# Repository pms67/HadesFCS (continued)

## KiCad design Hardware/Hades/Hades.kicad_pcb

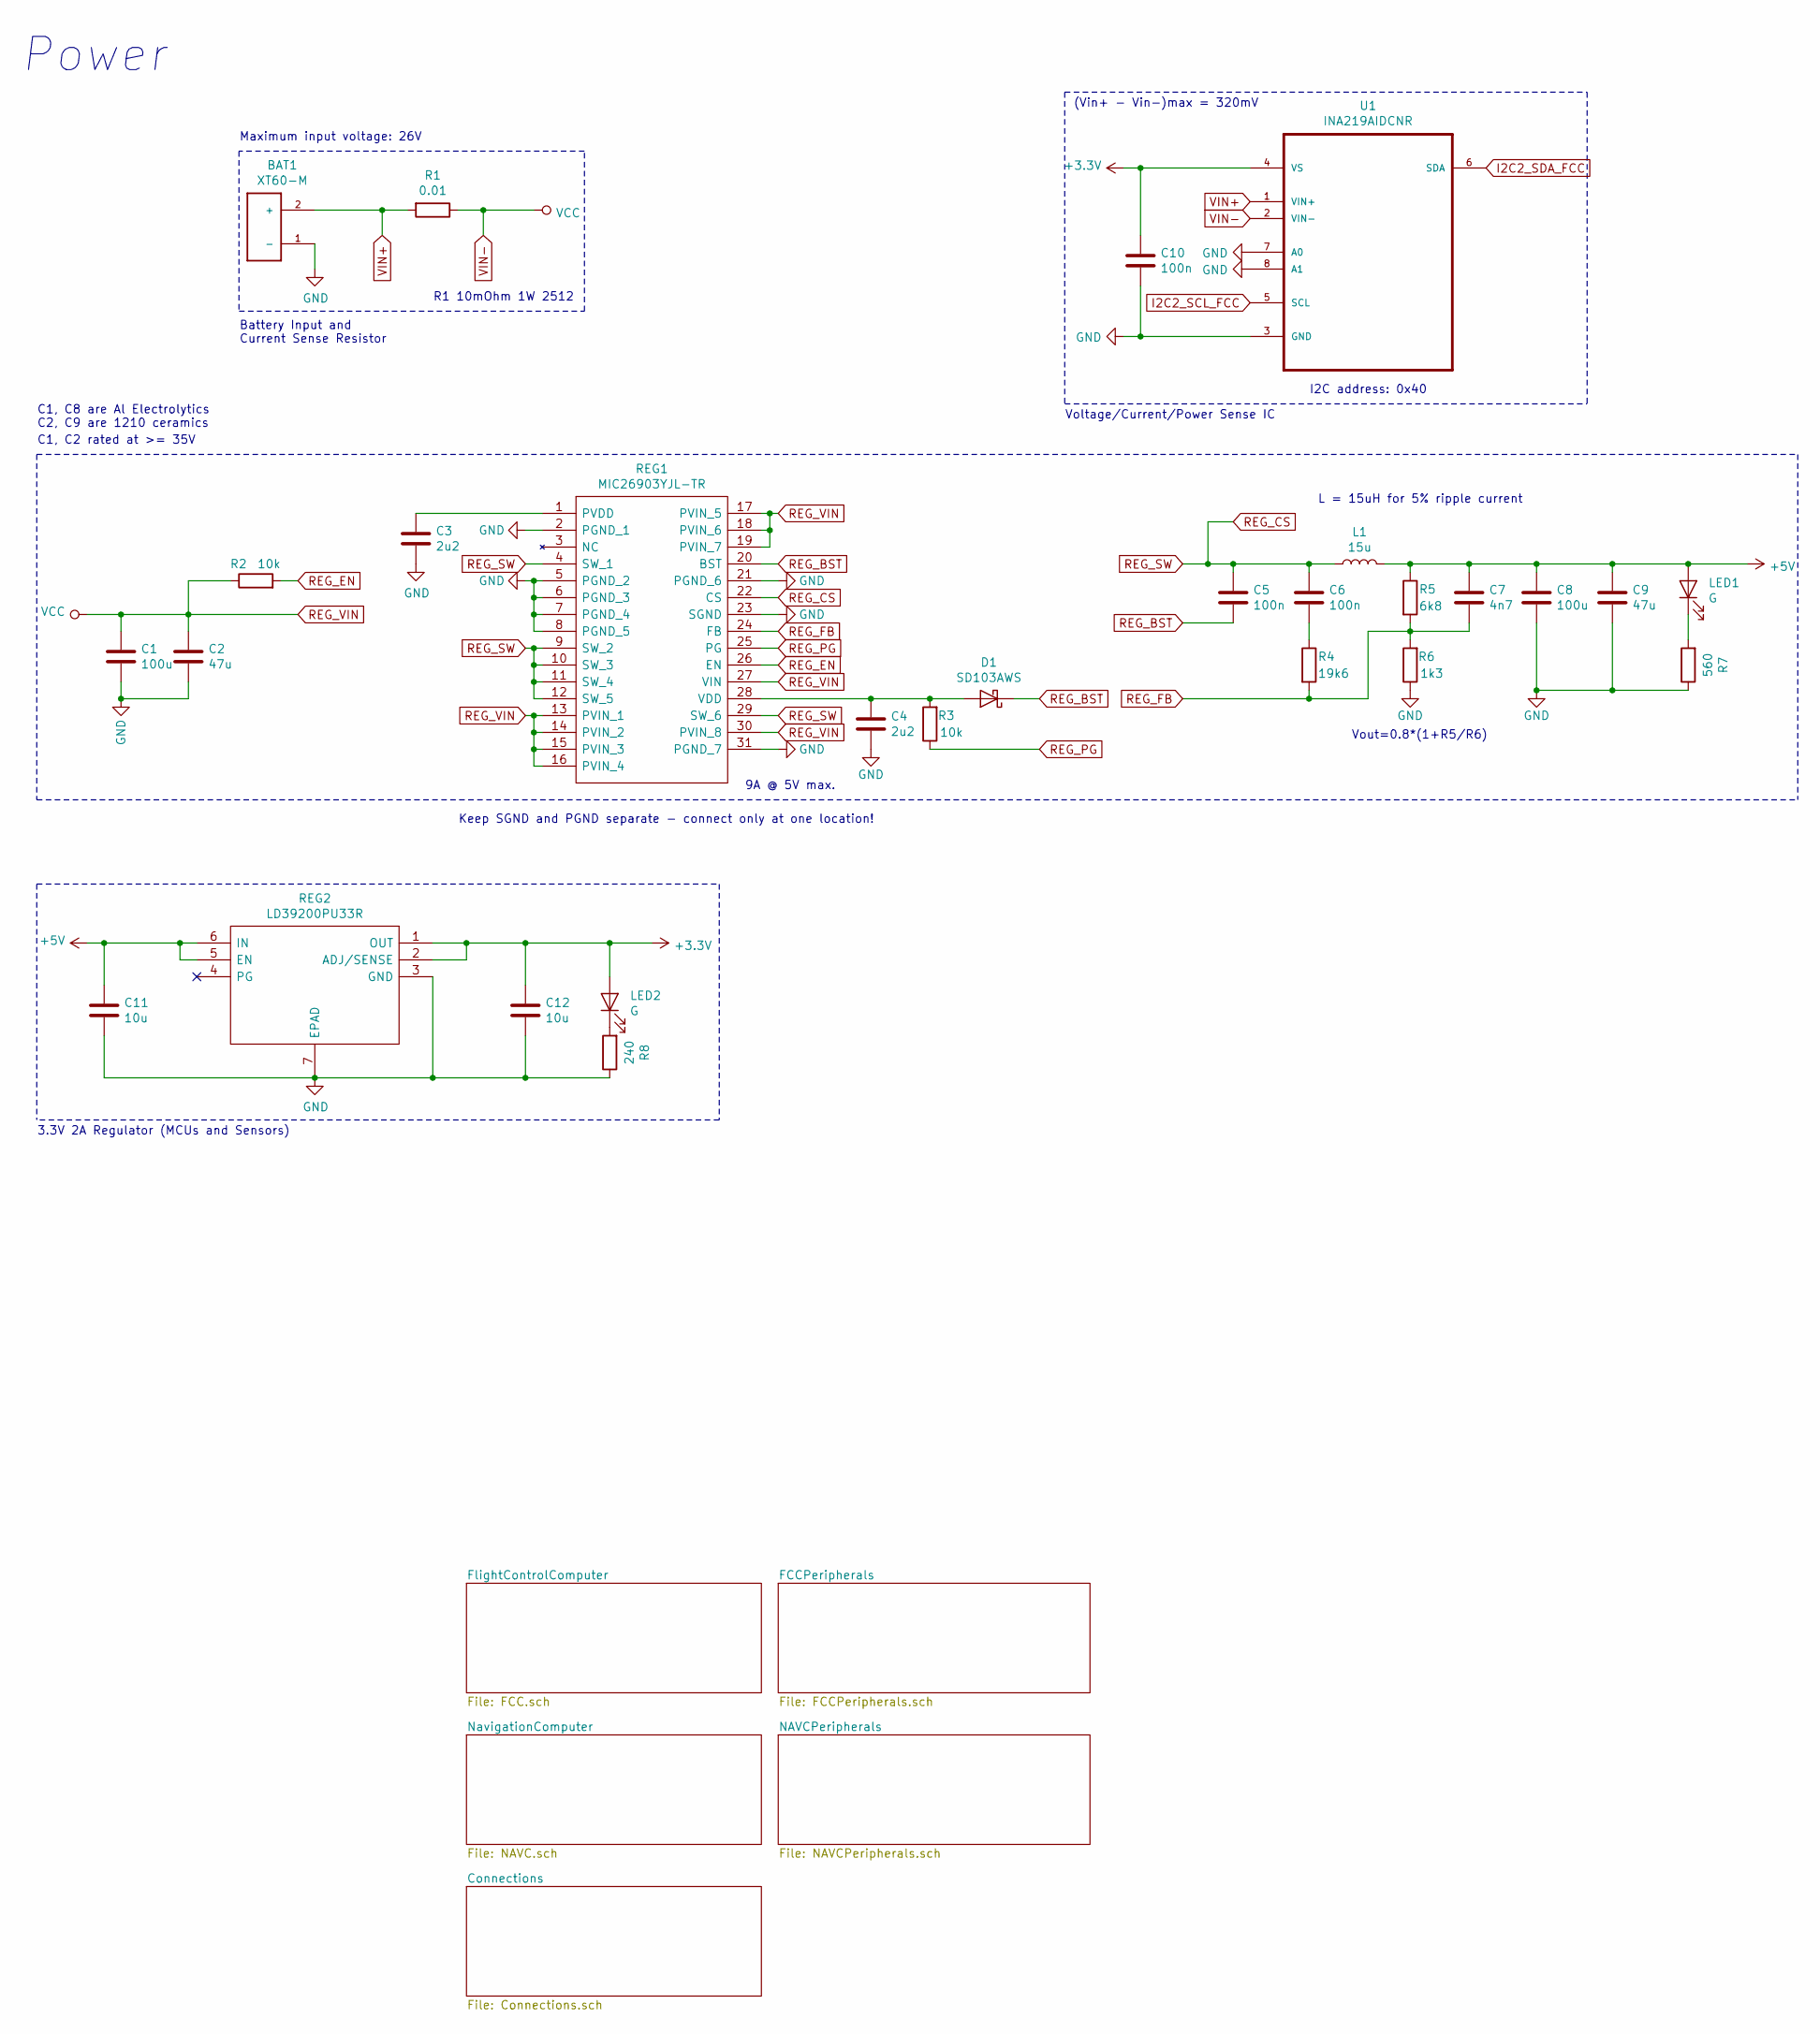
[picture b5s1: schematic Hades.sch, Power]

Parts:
BAT1: XT60-M; AMASS_XT60-M
C1, C8: 100u; C_Elec_6.3x7.7
C2, C9: 47u; C_1210_3225Metric
C3, C4: 2u2; C_0805_2012Metric
C5, C6: 100n; C_0805_2012Metric
C7: 4n7; C_0805_2012Metric
C10: 100n; C_0402_1005Metric
C11, C12: 10u; C_0603_1608Metric
D1: SD103AWS; D_SOD-323
L1: 15u; INDPM135125X650N
LED1, LED2: G; LED_0603_1608Metric
R1: 0.01; R_2512_6332Metric
R2, R3: 10k; R_0805_2012Metric
R4: 19k6; R_0805_2012Metric
R5: 6k8; R_0805_2012Metric
R6: 1k3; R_0805_2012Metric
R7: 560; R_0603_1608Metric
R8: 240; R_0603_1608Metric
REG1: MIC26903YJL-TR; MIC24054YJLTR; Manufacturer_Part_Number MIC26903YJL-TR; Mouser Part Number 998-MIC26903YJLTR
REG2: LD39200PU33R; SON95P300X300X100-7N-D; Manufacturer_Part_Number LD39200PU33R; Mouser Part Number 511-LD39200PU33R
U1: INA219AIDCNR; SOT65P280X145-8N

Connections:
+5V: C7.1, C8.1, C9.1, C11.1, L1.2, LED1.2 (A), R5.1, REG2.5 (EN), REG2.6 (IN); also elsewhere on the board
GND: BAT1.1 (-), C1.2, C2.2, C3.2, C4.2, C8.2, C9.2, C10.2, C11.2, C12.2, R6.1, R7.1, R8.1, REG1.2 (PGND_1), REG1.5 (PGND_2), REG1.6 (PGND_3), REG1.7 (PGND_4), REG1.8 (PGND_5), REG1.21 (PGND_6), REG1.23 (SGND), REG1.31 (PGND_7), REG2.3 (GND), REG2.7 (EPAD), U1.3 (GND), U1.7 (A0), U1.8 (A1); also elsewhere on the board
I2C2_SCL_FCC: U1.5 (SCL); also elsewhere on the board
I2C2_SDA_FCC: U1.6 (SDA); also elsewhere on the board
unnamed: C3.1, REG1.1 (PVDD)
unnamed: C4.1, D1.2 (A), R3.2, REG1.28 (VDD)
unnamed: C6.2, R4.1
unnamed: LED1.1 (K), R7.2
unnamed: LED2.1 (K), R8.2
REG_BST: C5.2, D1.1 (K), REG1.20 (BST)
REG_CS: C5.1, C6.1, L1.1, REG1.4 (SW_1), REG1.9 (SW_2), REG1.10 (SW_3), REG1.11 (SW_4), REG1.12 (SW_5), REG1.22 (CS), REG1.29 (SW_6)
REG_EN: R2.2, REG1.26 (EN)
REG_FB: C7.2, R4.2, R5.2, R6.2, REG1.24 (FB)
REG_PG: R3.1, REG1.25 (PG)
REG_VIN: C1.1, C2.1, R1.1, R2.1, REG1.13 (PVIN_1), REG1.14 (PVIN_2), REG1.15 (PVIN_3), REG1.16 (PVIN_4), REG1.17 (PVIN_5), REG1.18 (PVIN_6), REG1.19 (PVIN_7), REG1.27 (VIN), REG1.30 (PVIN_8), U1.2 (VIN-)
VIN+: BAT1.2 (+), R1.2, U1.1 (VIN+)

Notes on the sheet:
I2C address: 0x40
Power
Battery Input and Current Sense Resistor
Voltage/Current/Power Sense IC
3.3V 2A Regulator (MCUs and Sensors)
C1, C8 are Al Electrolytics C2, C9 are 1210 ceramics
C1, C2 rated at >= 35V
R1 10mOhm 1W 2512
(Vin+ - Vin-)max = 320mV
L = 15uH for 5% ripple current
Vout=0.8*(1+R5/R6)
Keep SGND and PGND separate - connect only at one location!
Maximum input voltage: 26V
9A @ 5V max.

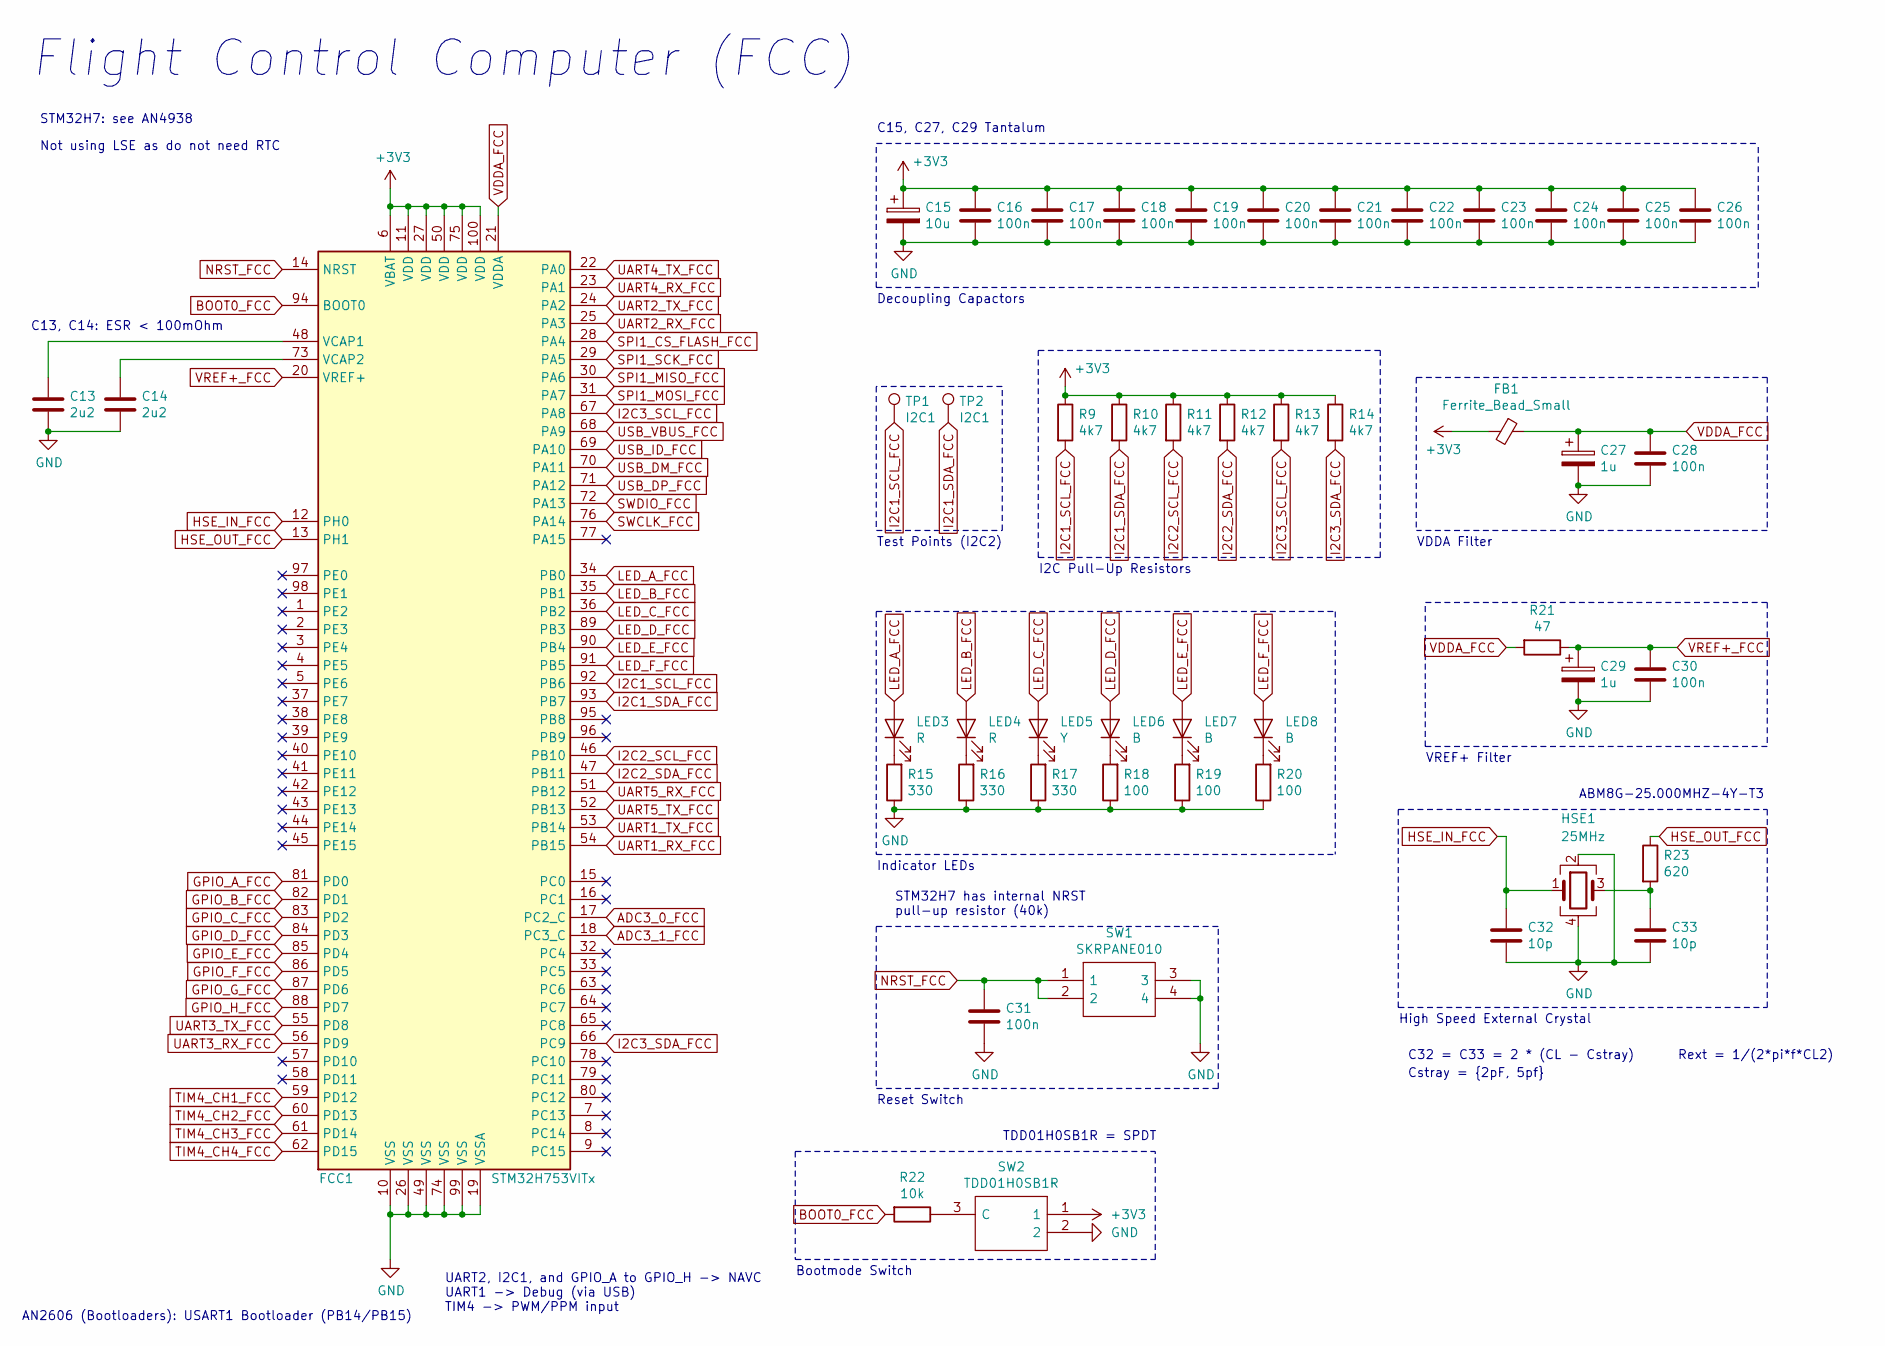
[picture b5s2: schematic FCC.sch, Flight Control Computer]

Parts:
C13, C14: 2u2; C_0603_1608Metric
C15: 10u; C_0603_1608Metric
C16, C17, C18, C19, C20, C21, C22, C23, C24, C25, C26, C28, C30, C31: 100n; C_0402_1005Metric
C27, C29: 1u; C_0603_1608Metric
C32, C33: 10p; C_0402_1005Metric
FB1: Ferrite_Bead_Small; L_0402_1005Metric
FCC1: STM32H753VITx; LQFP-100_14x14mm_P0.5mm
HSE1: 25MHz; Crystal_SMD_Abracon_ABM8G-4Pin_3.2x2.5mm
LED3, LED4: R; LED_0603_1608Metric
LED5: Y; LED_0603_1608Metric
LED6, LED7, LED8: B; LED_0603_1608Metric
R9, R10, R11, R12, R13, R14: 4k7; R_0402_1005Metric
R15, R16, R17: 330; R_0603_1608Metric
R18, R19, R20: 100; R_0603_1608Metric
R21: 47; R_0402_1005Metric
R22: 10k; R_0402_1005Metric
R23: 620; R_0603_1608Metric
SW1: SKRPANE010; SKRPADE010; Manufacturer_Part_Number SKRPANE010; Mouser Part Number 688-SKRPANE010
SW2: TDD01H0SB1R; SOT175P420X230-3N; Manufacturer_Part_Number TDD01H0SB1R; Mouser Part Number 611-TDD01H0SB1R
TP1, TP2: I2C1; TestPoint_Pad_D1.5mm

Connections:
BOOT0_FCC: FCC1.94 (BOOT0), R22.2; also elsewhere on the board
GND: C13.2, C14.2, C15.2, C16.2, C17.2, C18.2, C19.2, C20.2, C21.2, C22.2, C23.2, C24.2, C25.2, C26.2, C27.2, C28.2, C29.2, C30.2, C31.2, C32.2, C33.2, FCC1.10 (VSS), FCC1.19 (VSSA), FCC1.26 (VSS), FCC1.49 (VSS), FCC1.74 (VSS), FCC1.99 (VSS), HSE1.2, HSE1.4, R15.1, R16.1, R17.1, R18.1, R19.1, R20.1, SW1.3, SW1.4, SW2.2; also elsewhere on the board
HSE_IN_FCC: C32.1, FCC1.12 (PH0), HSE1.1; also elsewhere on the board
HSE_OUT_FCC: FCC1.13 (PH1), R23.1; also elsewhere on the board
I2C1_SCL_FCC: FCC1.92 (PB6), R9.2, TP1.1; also elsewhere on the board
I2C1_SDA_FCC: FCC1.93 (PB7), R10.2, TP2.1; also elsewhere on the board
I2C2_SCL_FCC: FCC1.46 (PB10), R11.2; also elsewhere on the board
I2C2_SDA_FCC: FCC1.47 (PB11), R12.2; also elsewhere on the board
I2C3_SCL_FCC: FCC1.67 (PA8), R13.2; also elsewhere on the board
I2C3_SDA_FCC: FCC1.66 (PC9), R14.2; also elsewhere on the board
LED_A_FCC: FCC1.34 (PB0), LED3.2 (A); also elsewhere on the board
LED_B_FCC: FCC1.35 (PB1), LED4.2 (A); also elsewhere on the board
LED_C_FCC: FCC1.36 (PB2), LED5.2 (A); also elsewhere on the board
LED_D_FCC: FCC1.89 (PB3), LED6.2 (A); also elsewhere on the board
LED_E_FCC: FCC1.90 (PB4), LED7.2 (A); also elsewhere on the board
LED_F_FCC: FCC1.91 (PB5), LED8.2 (A); also elsewhere on the board
NRST_FCC: C31.1, FCC1.14 (NRST), SW1.1, SW1.2; also elsewhere on the board
unnamed 65: C13.1, FCC1.48 (VCAP1); also elsewhere on the board
unnamed 66: C14.1, FCC1.73 (VCAP2); also elsewhere on the board
unnamed: C33.1, HSE1.3, R23.2
unnamed: LED3.1 (K), R15.2
unnamed: LED4.1 (K), R16.2
unnamed: LED5.1 (K), R17.2
unnamed: LED6.1 (K), R18.2
unnamed: LED7.1 (K), R19.2
unnamed: LED8.1 (K), R20.2
unnamed: R22.1, SW2.3 (C)
VDDA_FCC: C27.1, C28.1, FB1.1, FCC1.21 (VDDA), R21.2; also elsewhere on the board
VREF+_FCC: C29.1, C30.1, FCC1.20 (VREF+), R21.1; also elsewhere on the board

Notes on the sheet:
Flight Control Computer (FCC)
C13, C14: ESR < 100mOhm
STM32H7: see AN4938
C15, C27, C29 Tantalum
STM32H7 has internal NRST pull-up resistor (40k)
Not using LSE as do not need RTC
C32 = C33 = 2 * (CL - Cstray)
Cstray = {2pF, 5pf}
UART2, I2C1, and GPIO_A to GPIO_H -> NAVC UART1 -> Debug (via USB) TIM4 -> PWM/PPM input
Decoupling Capactors
VDDA Filter
VREF+ Filter
Reset Switch
Indicator LEDs
Bootmode Switch
High Speed External Crystal
I2C Pull-Up Resistors
Test Points (I2C2)
ABM8G-25.000MHZ-4Y-T3
TDD01H0SB1R = SPDT
AN2606 (Bootloaders): USART1 Bootloader (PB14/PB15)
Rext = 1/(2*pi*f*CL2)

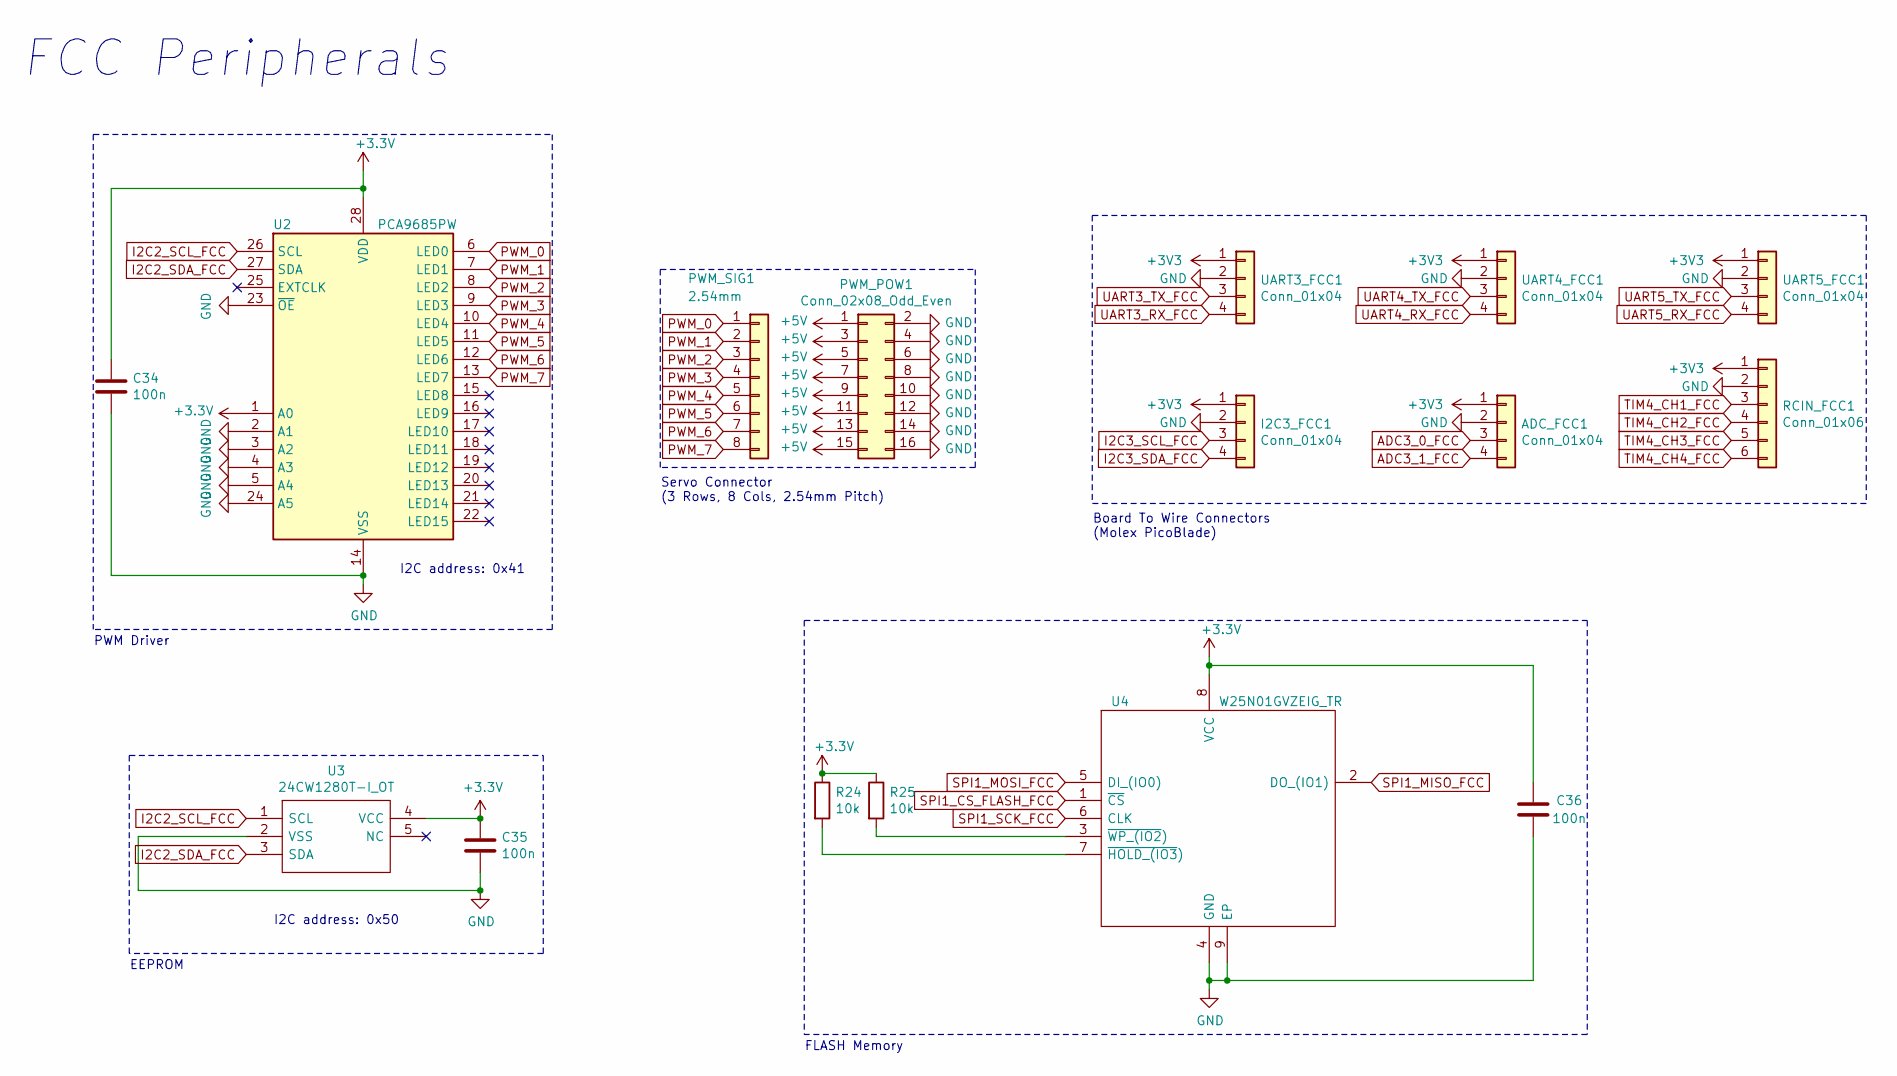
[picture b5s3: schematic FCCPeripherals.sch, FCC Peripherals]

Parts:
ADC_FCC1: Conn_01x04; Molex_PicoBlade_53048-0410_1x04_P1.25mm_Horizontal
C34, C35, C36: 100n; C_0402_1005Metric
I2C3_FCC1: Conn_01x04; Molex_PicoBlade_53048-0410_1x04_P1.25mm_Horizontal
PWM_POW1: Conn_02x08_Odd_Even; PinHeader_2x08_P2.54mm_Vertical
PWM_SIG1: 2.54mm; PinHeader_1x08_P2.54mm_Vertical
R24, R25: 10k; R_0402_1005Metric
RCIN_FCC1: Conn_01x06; Molex_PicoBlade_53048-0610_1x06_P1.25mm_Horizontal
U2: PCA9685PW; TSSOP-28_4.4x9.7mm_P0.65mm
U3: 24CW1280T-I_OT; SOT95P280X145-5N; Manufacturer_Part_Number 24CW1280T-I/OT; Mouser Part Number 579-24CW1280T-I/OT
U4: W25N01GVZEIG_TR; SON127P800X600X80-9N-D; Manufacturer_Part_Number W25N01GVZEIG TR; Mouser Part Number 454-W25N01GVZEIGTR
UART3_FCC1, UART4_FCC1, UART5_FCC1: Conn_01x04; Molex_PicoBlade_53048-0410_1x04_P1.25mm_Horizontal

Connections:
+5V: PWM_POW1.1, PWM_POW1.3, PWM_POW1.5, PWM_POW1.7, PWM_POW1.9, PWM_POW1.11, PWM_POW1.13, PWM_POW1.15; also elsewhere on the board
GND: ADC_FCC1.2, C34.2, C35.2, C36.1, I2C3_FCC1.2, PWM_POW1.2, PWM_POW1.4, PWM_POW1.6, PWM_POW1.8, PWM_POW1.10, PWM_POW1.12, PWM_POW1.14, PWM_POW1.16, RCIN_FCC1.2, U2.2 (A1), U2.3 (A2), U2.4 (A3), U2.5 (A4), U2.14 (VSS), U2.23 (~OE), U2.24 (A5), U3.2 (VSS), U4.4 (GND), U4.9 (EP), UART3_FCC1.2, UART4_FCC1.2, UART5_FCC1.2; also elsewhere on the board
I2C2_SCL_FCC: U2.26 (SCL), U3.1 (SCL); also elsewhere on the board
I2C2_SDA_FCC: U2.27 (SDA), U3.3 (SDA); also elsewhere on the board
unnamed: ADC_FCC1.1, I2C3_FCC1.1, RCIN_FCC1.1, UART3_FCC1.1, UART4_FCC1.1, UART5_FCC1.1
unnamed: R24.2, U4.7 (~HOLD_(IO3))
unnamed: R25.2, U4.3 (~WP_(IO2))
PWM_0: PWM_SIG1.1, U2.6 (LED0)
PWM_1: PWM_SIG1.2, U2.7 (LED1)
PWM_2: PWM_SIG1.3, U2.8 (LED2)
PWM_3: PWM_SIG1.4, U2.9 (LED3)
PWM_4: PWM_SIG1.5, U2.10 (LED4)
PWM_5: PWM_SIG1.6, U2.11 (LED5)
PWM_6: PWM_SIG1.7, U2.12 (LED6)
PWM_7: PWM_SIG1.8, U2.13 (LED7)
SPI1_CS_FLASH_FCC: U4.1 (~CS); also elsewhere on the board
SPI1_MISO_FCC: U4.2 (DO_(IO1)); also elsewhere on the board
SPI1_MOSI_FCC: U4.5 (DI_(IO0)); also elsewhere on the board
SPI1_SCK_FCC: U4.6 (CLK); also elsewhere on the board

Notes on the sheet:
I2C address: 0x41
I2C address: 0x50
FCC Peripherals
PWM Driver
Servo Connector (3 Rows, 8 Cols, 2.54mm Pitch)
Board To Wire Connectors (Molex PicoBlade)
EEPROM
FLASH Memory

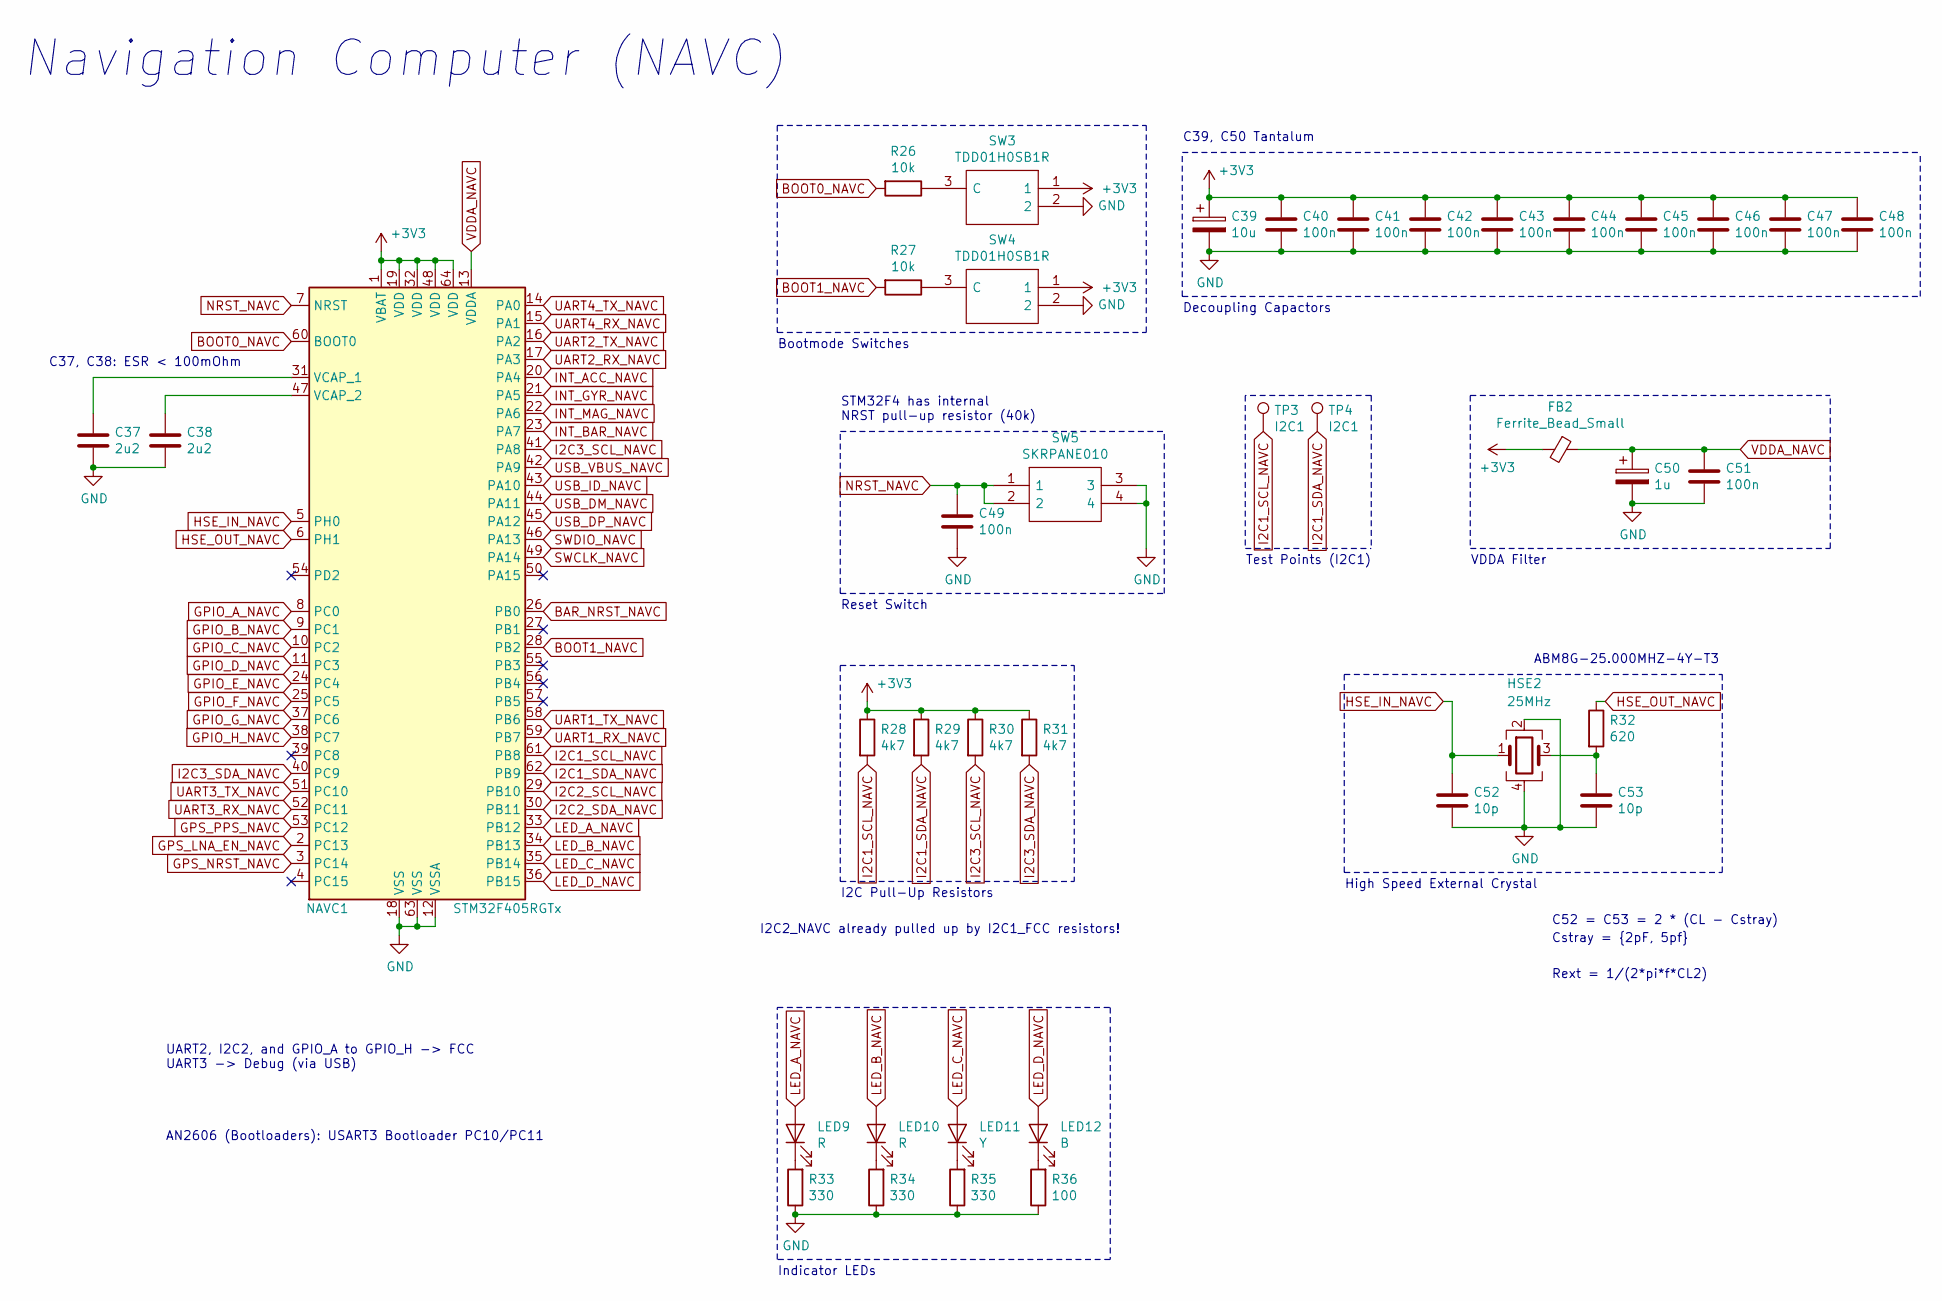
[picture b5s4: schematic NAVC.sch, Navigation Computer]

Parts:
C37, C38: 2u2; C_0603_1608Metric
C39: 10u; C_0603_1608Metric
C40, C41, C42, C43, C44, C45, C46, C47, C48, C49, C51: 100n; C_0402_1005Metric
C50: 1u; C_0603_1608Metric
C52, C53: 10p; C_0402_1005Metric
FB2: Ferrite_Bead_Small; L_0402_1005Metric
HSE2: 25MHz; Crystal_SMD_Abracon_ABM8G-4Pin_3.2x2.5mm
LED9, LED10: R; LED_0603_1608Metric
LED11: Y; LED_0603_1608Metric
LED12: B; LED_0603_1608Metric
NAVC1: STM32F405RGTx; LQFP-64_10x10mm_P0.5mm
R26, R27: 10k; R_0402_1005Metric
R28, R29, R30, R31: 4k7; R_0402_1005Metric
R32: 620; R_0603_1608Metric
R33, R34, R35: 330; R_0603_1608Metric
R36: 100; R_0603_1608Metric
SW3, SW4: TDD01H0SB1R; SOT175P420X230-3N; Manufacturer_Part_Number TDD01H0SB1R; Mouser Part Number 611-TDD01H0SB1R
SW5: SKRPANE010; SKRPADE010; Manufacturer_Part_Number SKRPANE010; Mouser Part Number 688-SKRPANE010
TP3, TP4: I2C1; TestPoint_Pad_D1.5mm

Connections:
BOOT0_NAVC: NAVC1.60 (BOOT0), R26.2; also elsewhere on the board
BOOT1_NAVC: NAVC1.28 (PB2), R27.2; also elsewhere on the board
GND: C37.2, C38.2, C39.2, C40.2, C41.2, C42.2, C43.2, C44.2, C45.2, C46.2, C47.2, C48.2, C49.2, C50.2, C51.2, C52.2, C53.2, HSE2.2, HSE2.4, NAVC1.12 (VSSA), NAVC1.18 (VSS), NAVC1.63 (VSS), R33.1, R34.1, R35.1, R36.1, SW3.2, SW4.2, SW5.3, SW5.4; also elsewhere on the board
HSE_IN_NAVC: C52.1, HSE2.1, NAVC1.5 (PH0); also elsewhere on the board
HSE_OUT_NAVC: NAVC1.6 (PH1), R32.1; also elsewhere on the board
I2C1_SCL_NAVC: NAVC1.61 (PB8), R28.2, TP3.1; also elsewhere on the board
I2C1_SDA_NAVC: NAVC1.62 (PB9), R29.2, TP4.1; also elsewhere on the board
I2C3_SCL_NAVC: NAVC1.41 (PA8), R30.2; also elsewhere on the board
I2C3_SDA_NAVC: NAVC1.40 (PC9), R31.2; also elsewhere on the board
LED_A_NAVC: LED9.2 (A), NAVC1.33 (PB12); also elsewhere on the board
LED_B_NAVC: LED10.2 (A), NAVC1.34 (PB13); also elsewhere on the board
LED_C_NAVC: LED11.2 (A), NAVC1.35 (PB14); also elsewhere on the board
LED_D_NAVC: LED12.2 (A), NAVC1.36 (PB15); also elsewhere on the board
NRST_NAVC: C49.1, NAVC1.7 (NRST), SW5.1, SW5.2; also elsewhere on the board
unnamed 68: C37.1, NAVC1.31 (VCAP_1); also elsewhere on the board
unnamed 69: C38.1, NAVC1.47 (VCAP_2); also elsewhere on the board
unnamed: C53.1, HSE2.3, R32.2
unnamed: LED9.1 (K), R33.2
unnamed: LED10.1 (K), R34.2
unnamed: LED11.1 (K), R35.2
unnamed: LED12.1 (K), R36.2
unnamed: R26.1, SW3.3 (C)
unnamed: R27.1, SW4.3 (C)
VDDA_NAVC: C50.1, C51.1, FB2.1, NAVC1.13 (VDDA); also elsewhere on the board

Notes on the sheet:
Navigation Computer (NAVC)
C39, C50 Tantalum
STM32F4 has internal NRST pull-up resistor (40k)
C52 = C53 = 2 * (CL - Cstray)
Cstray = {2pF, 5pf}
Decoupling Capactors
VDDA Filter
Reset Switch
Indicator LEDs
Bootmode Switches
High Speed External Crystal
I2C Pull-Up Resistors
Test Points (I2C1)
C37, C38: ESR < 100mOhm
UART2, I2C2, and GPIO_A to GPIO_H -> FCC UART3 -> Debug (via USB)
I2C2_NAVC already pulled up by I2C1_FCC resistors!
ABM8G-25.000MHZ-4Y-T3
AN2606 (Bootloaders): USART3 Bootloader PC10/PC11
Rext = 1/(2*pi*f*CL2)

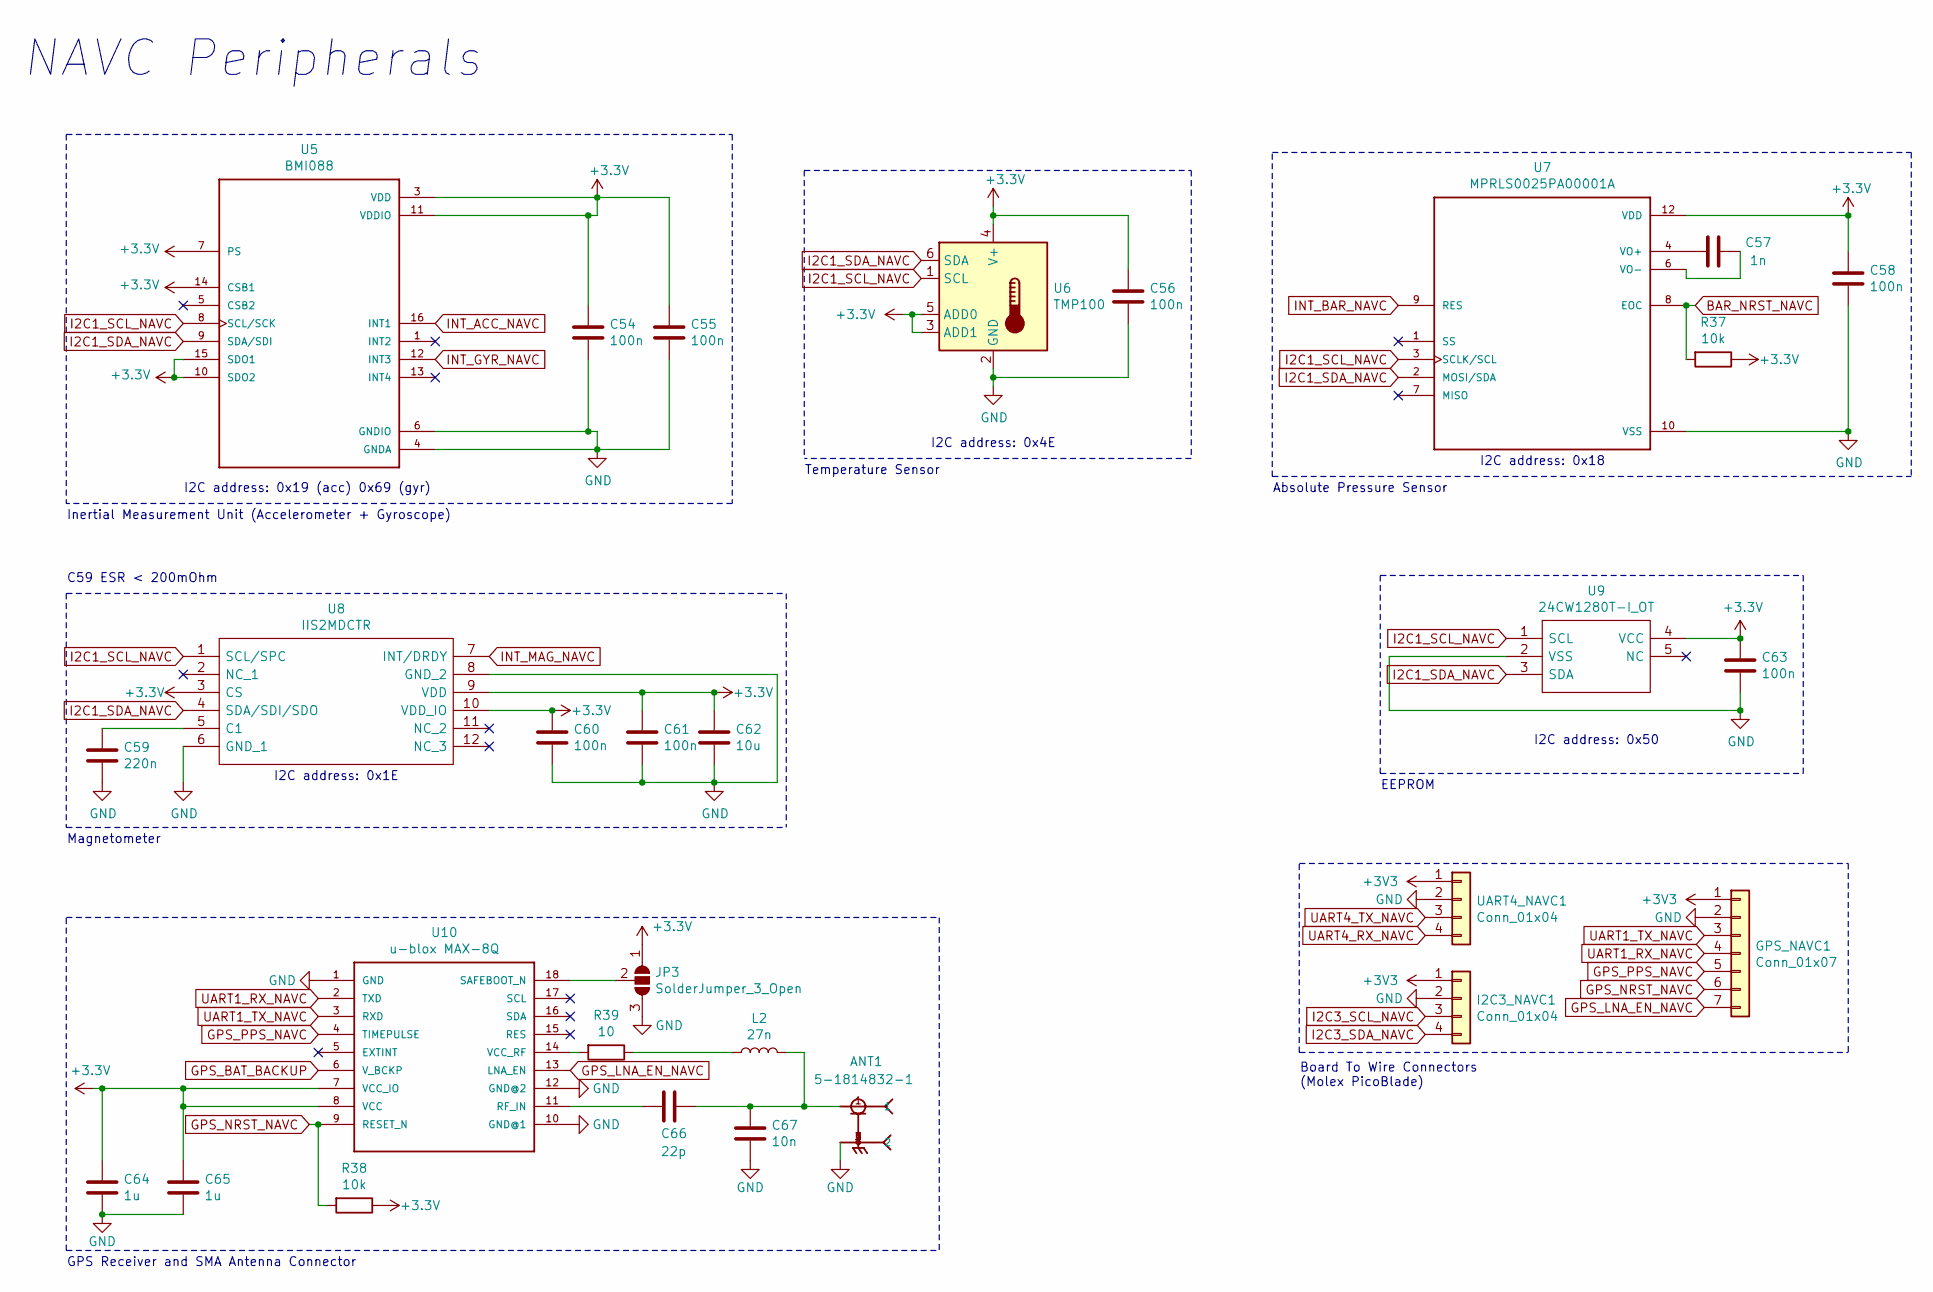
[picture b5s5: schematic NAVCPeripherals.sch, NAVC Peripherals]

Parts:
ANT1: 5-1814832-1; TE_5-1814832-1
C54, C55, C56, C58, C60, C61, C63: 100n; C_0402_1005Metric
C57: 1n; C_0402_1005Metric
C59: 220n; C_0603_1608Metric
C62: 10u; C_0603_1608Metric
C64, C65: 1u; C_0603_1608Metric
C66: 22p; C_0402_1005Metric
C67: 10n; C_0402_1005Metric
GPS_NAVC1: Conn_01x07; Molex_PicoBlade_53048-0710_1x07_P1.25mm_Horizontal
I2C3_NAVC1: Conn_01x04; Molex_PicoBlade_53048-0410_1x04_P1.25mm_Horizontal
JP3: SolderJumper_3_Open; SolderJumper-3_P1.3mm_Open_RoundedPad1.0x1.5mm
L2: 27n; L_0402_1005Metric
R37, R38: 10k; R_0402_1005Metric
R39: 10; R_0402_1005Metric
U5: BMI088; PQFN50P450X300X100-16N
U6: TMP100; SOT-23-6
U7: MPRLS0025PA00001A; XDCR_MPRLS0025PA00001A
U8: IIS2MDCTR; Manufacturer_Part_Number IIS2MDCTR; Mouser Part Number 511-IIS2MDCTR
U9: 24CW1280T-I_OT; SOT95P280X145-5N; Manufacturer_Part_Number 24CW1280T-I/OT; Mouser Part Number 579-24CW1280T-I/OT
U10: u-blox MAX-8Q; GPS18P-SMD-1.1-10X9.6MM
UART4_NAVC1: Conn_01x04; Molex_PicoBlade_53048-0410_1x04_P1.25mm_Horizontal

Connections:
BAR_NRST_NAVC: R37.2, U7.8 (EOC); also elsewhere on the board
GND: ANT1.2, ANT1.3 (2), ANT1.4 (2), ANT1.5 (2), C54.2, C55.2, C56.2, C58.2, C59.2, C60.2, C61.2, C62.2, C63.2, C64.2, C65.2, C67.2, GPS_NAVC1.2, I2C3_NAVC1.2, JP3.3 (B), U5.4 (GNDA), U5.6 (GNDIO), U6.2 (GND), U7.10 (VSS), U8.6 (GND_1), U8.8 (GND_2), U9.2 (VSS), U10.1 (GND), U10.10 (GND@1), U10.12 (GND@2), UART4_NAVC1.2; also elsewhere on the board
GPS_BAT_BACKUP: U10.6 (V_BCKP); also elsewhere on the board
GPS_LNA_EN_NAVC: GPS_NAVC1.7, U10.13 (LNA_EN); also elsewhere on the board
GPS_NRST_NAVC: GPS_NAVC1.6, R38.2, U10.9 (RESET_N); also elsewhere on the board
GPS_PPS_NAVC: GPS_NAVC1.5, U10.4 (TIMEPULSE); also elsewhere on the board
I2C1_SCL_NAVC: U5.8 (SCL/SCK), U6.1 (SCL), U7.3 (SCLK/SCL), U8.1 (SCL/SPC), U9.1 (SCL); also elsewhere on the board
I2C1_SDA_NAVC: U5.9 (SDA/SDI), U6.6 (SDA), U7.2 (MOSI/SDA), U8.4 (SDA/SDI/SDO), U9.3 (SDA); also elsewhere on the board
INT_ACC_NAVC: U5.16 (INT1); also elsewhere on the board
INT_BAR_NAVC: U7.9 (RES); also elsewhere on the board
INT_GYR_NAVC: U5.12 (INT3); also elsewhere on the board
INT_MAG_NAVC: U8.7 (INT/DRDY); also elsewhere on the board
unnamed: ANT1.1, C66.1, C67.1, L2.2
unnamed: C57.1, U7.6 (VO-)
unnamed: C57.2, U7.4 (VO+)
unnamed: C59.1, U8.5 (C1)
unnamed: C66.2, U10.11 (RF_IN)
unnamed: GPS_NAVC1.1, I2C3_NAVC1.1, UART4_NAVC1.1
unnamed: JP3.2 (C), U10.18 (SAFEBOOT_N)
unnamed: L2.1, R39.1
unnamed: R39.2, U10.14 (VCC_RF)
UART1_RX_NAVC: GPS_NAVC1.4, U10.2 (TXD); also elsewhere on the board
UART1_TX_NAVC: GPS_NAVC1.3, U10.3 (RXD); also elsewhere on the board

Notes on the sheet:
I2C address: 0x19 (acc) 0x69 (gyr)
NAVC Peripherals
Inertial Measurement Unit (Accelerometer + Gyroscope)
I2C address: 0x4E
Temperature Sensor
I2C address: 0x50
EEPROM
I2C address: 0x1E
C59 ESR < 200mOhm
Magnetometer
I2C address: 0x18
Absolute Pressure Sensor
GPS Receiver and SMA Antenna Connector
Board To Wire Connectors (Molex PicoBlade)
